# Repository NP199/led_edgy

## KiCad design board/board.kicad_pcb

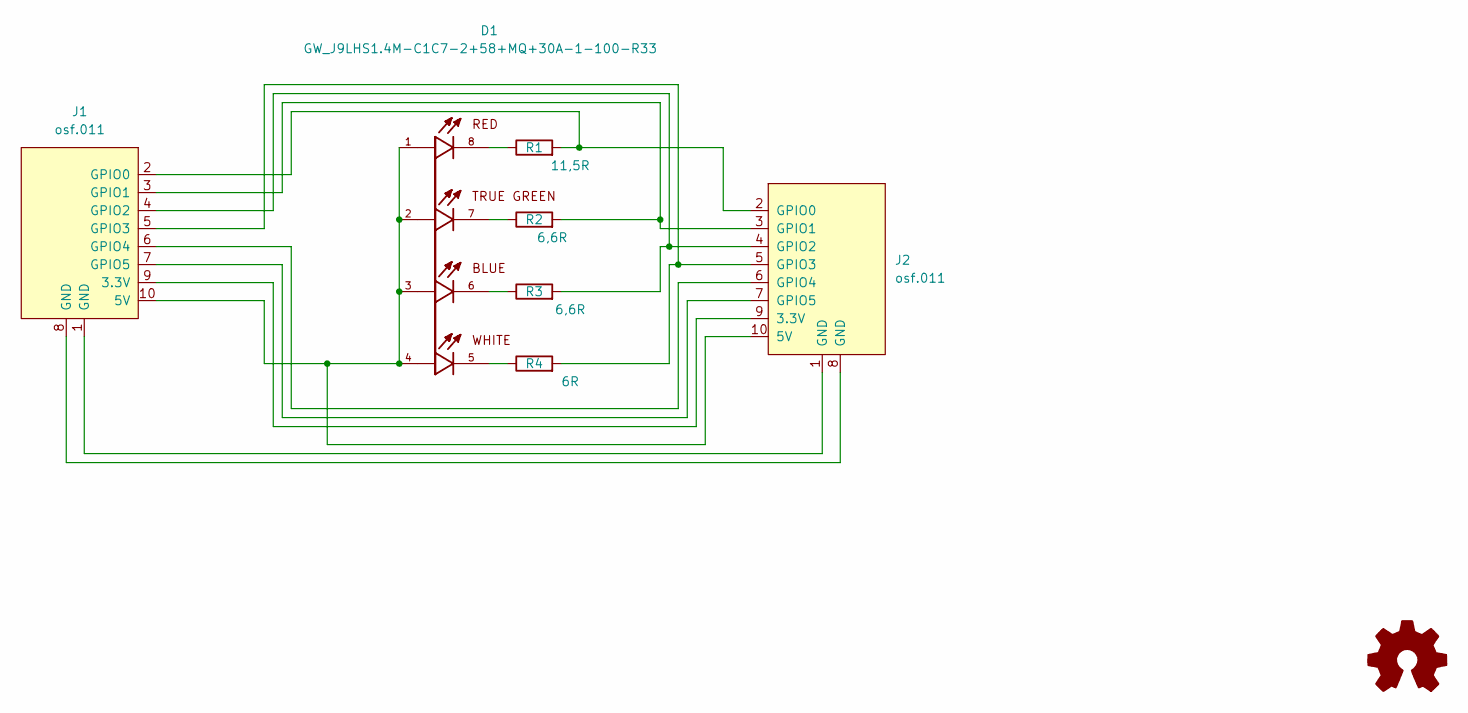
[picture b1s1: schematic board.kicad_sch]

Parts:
D1: GW_J9LHS1.4M-C1C7-2+58+MQ+30A-1-100-R33; LED_GW_J9LHS1.4M-C1C7-2+58+MQ+30A-1-100-R33; PARTREV 1.2
J1: osf.011; on_edge_2x05_device
J2: osf.011; on_edge_2x05_host
LOGO1: Logo_Open_Hardware_Small; OSHW-Symbol_6.7x6mm_SilkScreen
R1: 11,5R; R_0805_2012Metric_Pad1.20x1.40mm_HandSolder
R2, R3: 6,6R; R_0603_1608Metric_Pad0.98x0.95mm_HandSolder
R4: 6R; R_0603_1608Metric_Pad0.98x0.95mm_HandSolder

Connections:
unnamed: D1.5, R4.1
unnamed: D1.6, R3.1
unnamed: D1.7, R2.1
unnamed: D1.8, R1.1
unnamed: J1.9 (3.3V), J2.9 (3.3V)
unnamed: D1.1, D1.2, D1.3, D1.4, J1.10 (5V), J2.10 (5V)
unnamed: J1.1 (GND), J2.1 (GND)
unnamed: J1.8 (GND), J2.8 (GND)
unnamed: J1.2 (GPIO0), J2.2 (GPIO0), R1.2
unnamed: J1.3 (GPIO1), J2.3 (GPIO1), R2.2
unnamed: J1.4 (GPIO2), J2.4 (GPIO2), R3.2
unnamed: J1.5 (GPIO3), J2.5 (GPIO3), R4.2
unnamed: J1.6 (GPIO4), J2.6 (GPIO4)
unnamed: J1.7 (GPIO5), J2.7 (GPIO5)

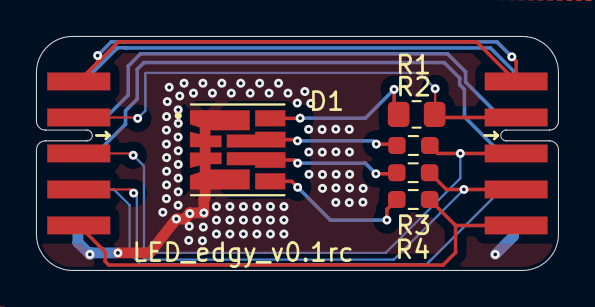
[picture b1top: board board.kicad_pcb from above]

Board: 4 copper layers, 29.0 x 13.0 mm, 8 parts (1 on the bottom side), 14 nets.

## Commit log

2023-05-23 Update surface and connected vias | Change common ground to common anode
2023-05-25 Update Layout | Remove DRC Errors | Connected unused Edgy Pins
2023-05-26 Change edgy connector back to GPIO | Began adding Resistor to specific voltage
2023-05-28 Increase PCB size | Update Design
2023-05-28 Add value to resistor
2023-05-28 Add footrpint, symbol and 3d model
2023-05-28 Add open hardware logo
2023-05-28 Add silkscreen for identification
2023-05-30 Update Schmetaic Design for better heat management
2023-05-30 Save changes
2023-06-04 Update PCB Design | Add routes
